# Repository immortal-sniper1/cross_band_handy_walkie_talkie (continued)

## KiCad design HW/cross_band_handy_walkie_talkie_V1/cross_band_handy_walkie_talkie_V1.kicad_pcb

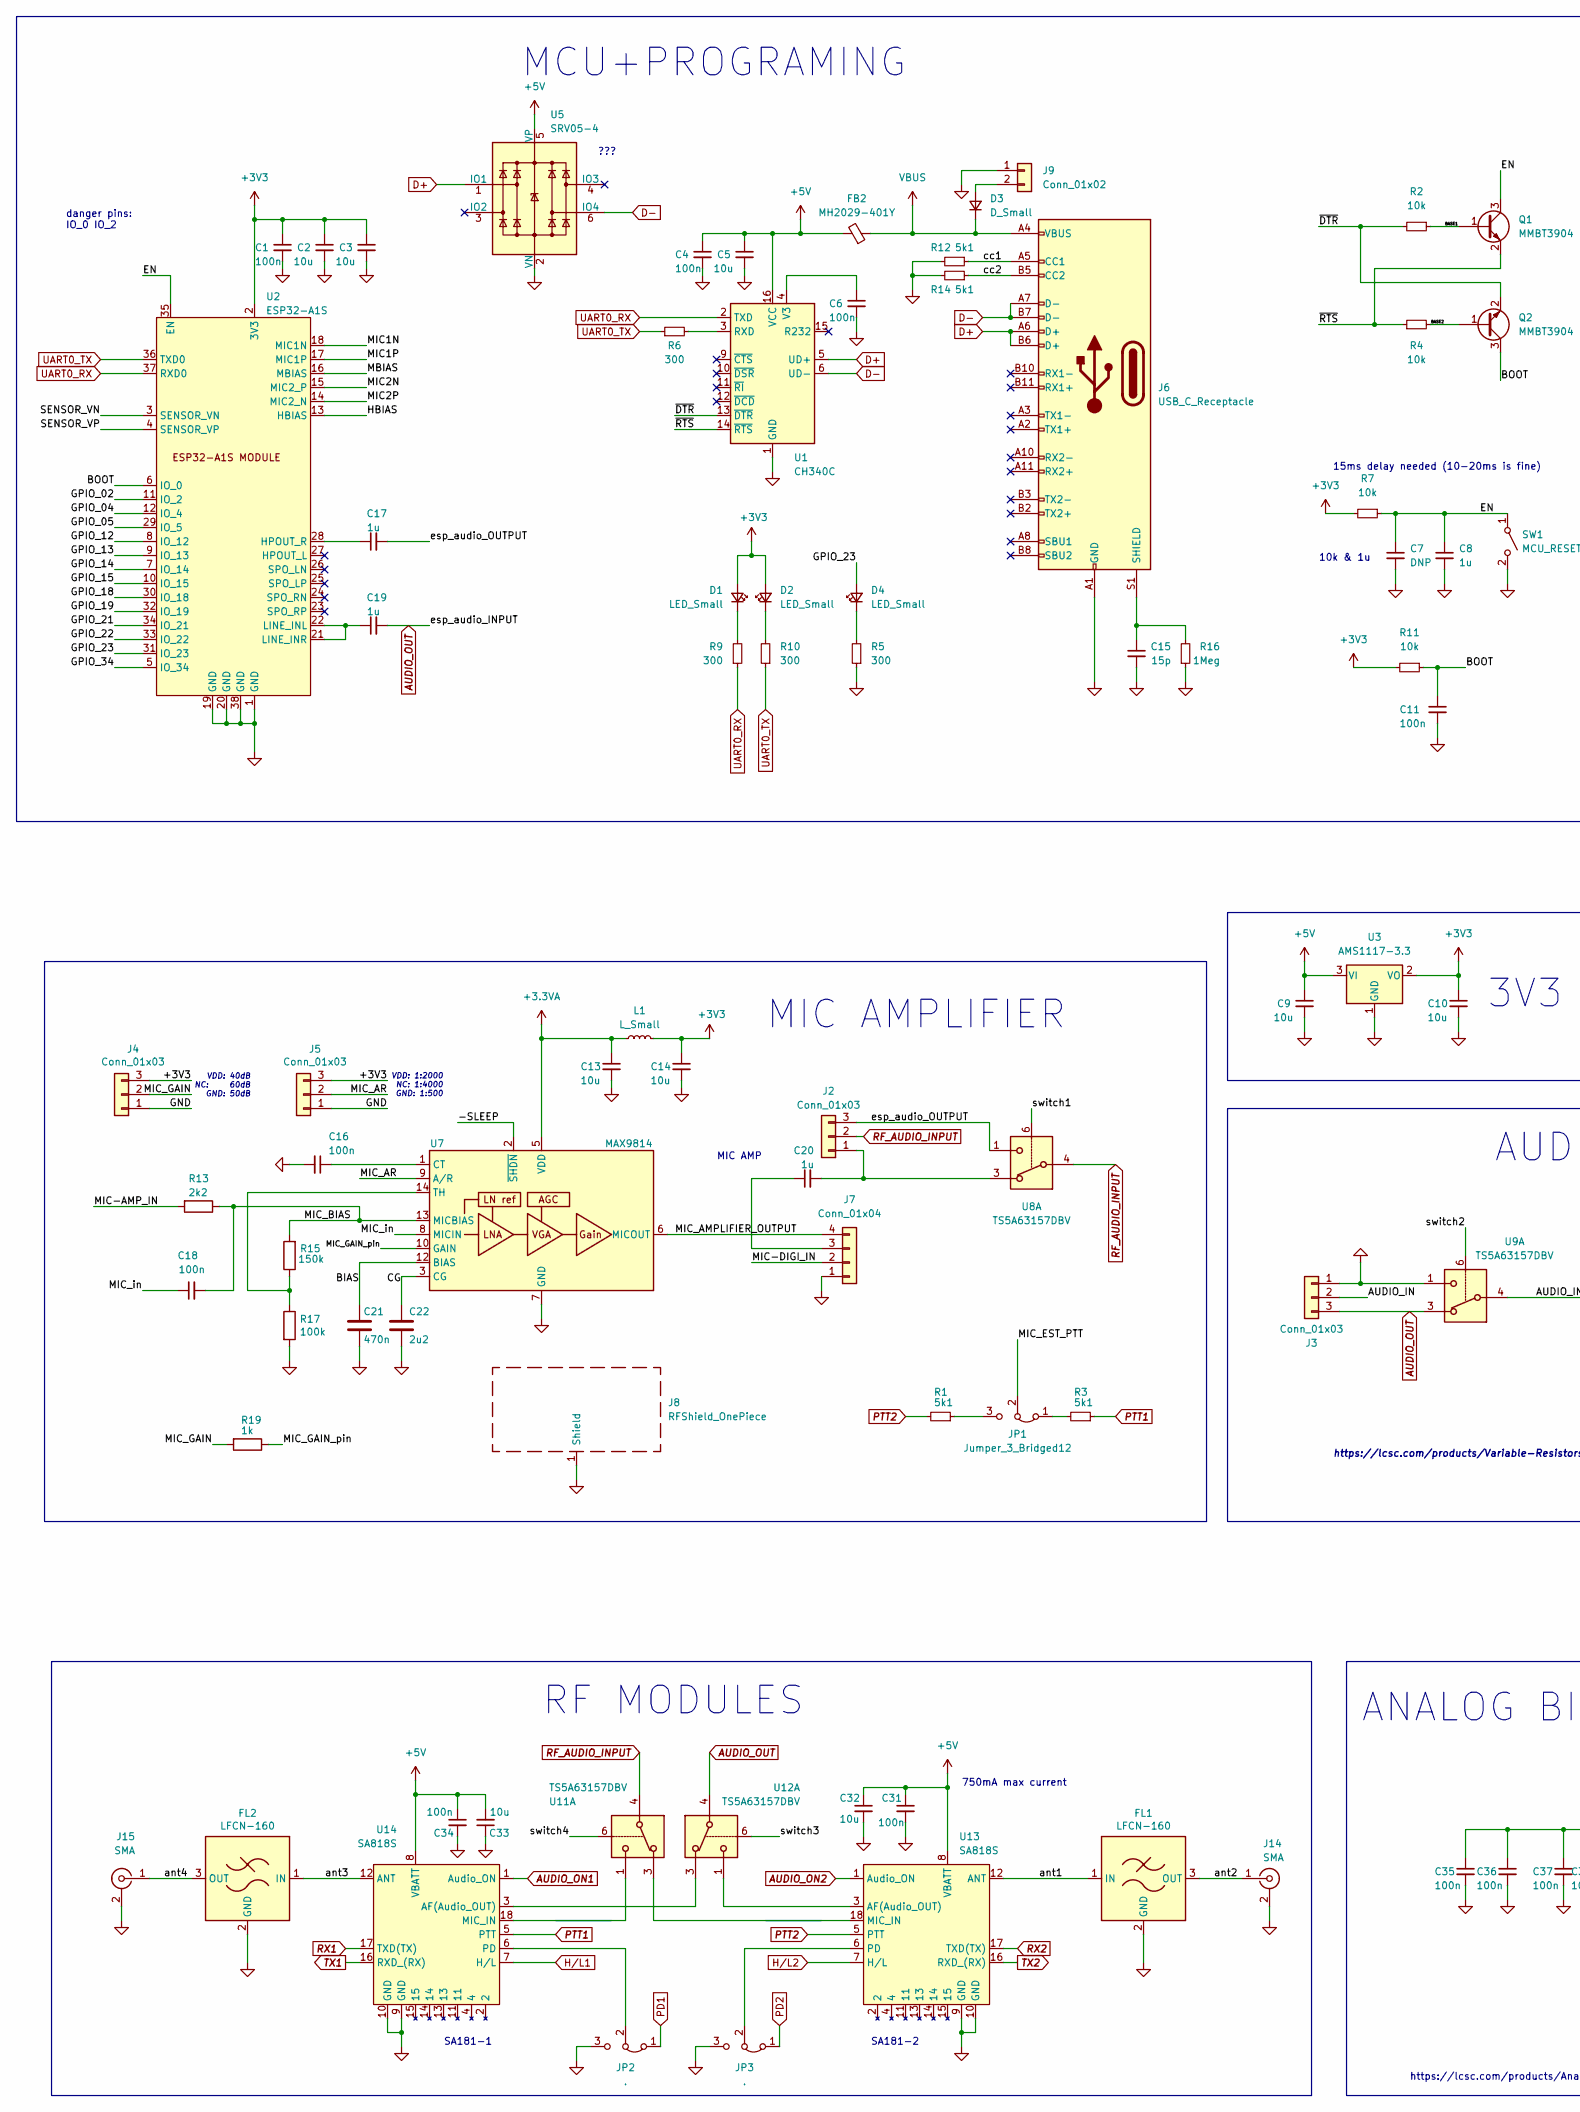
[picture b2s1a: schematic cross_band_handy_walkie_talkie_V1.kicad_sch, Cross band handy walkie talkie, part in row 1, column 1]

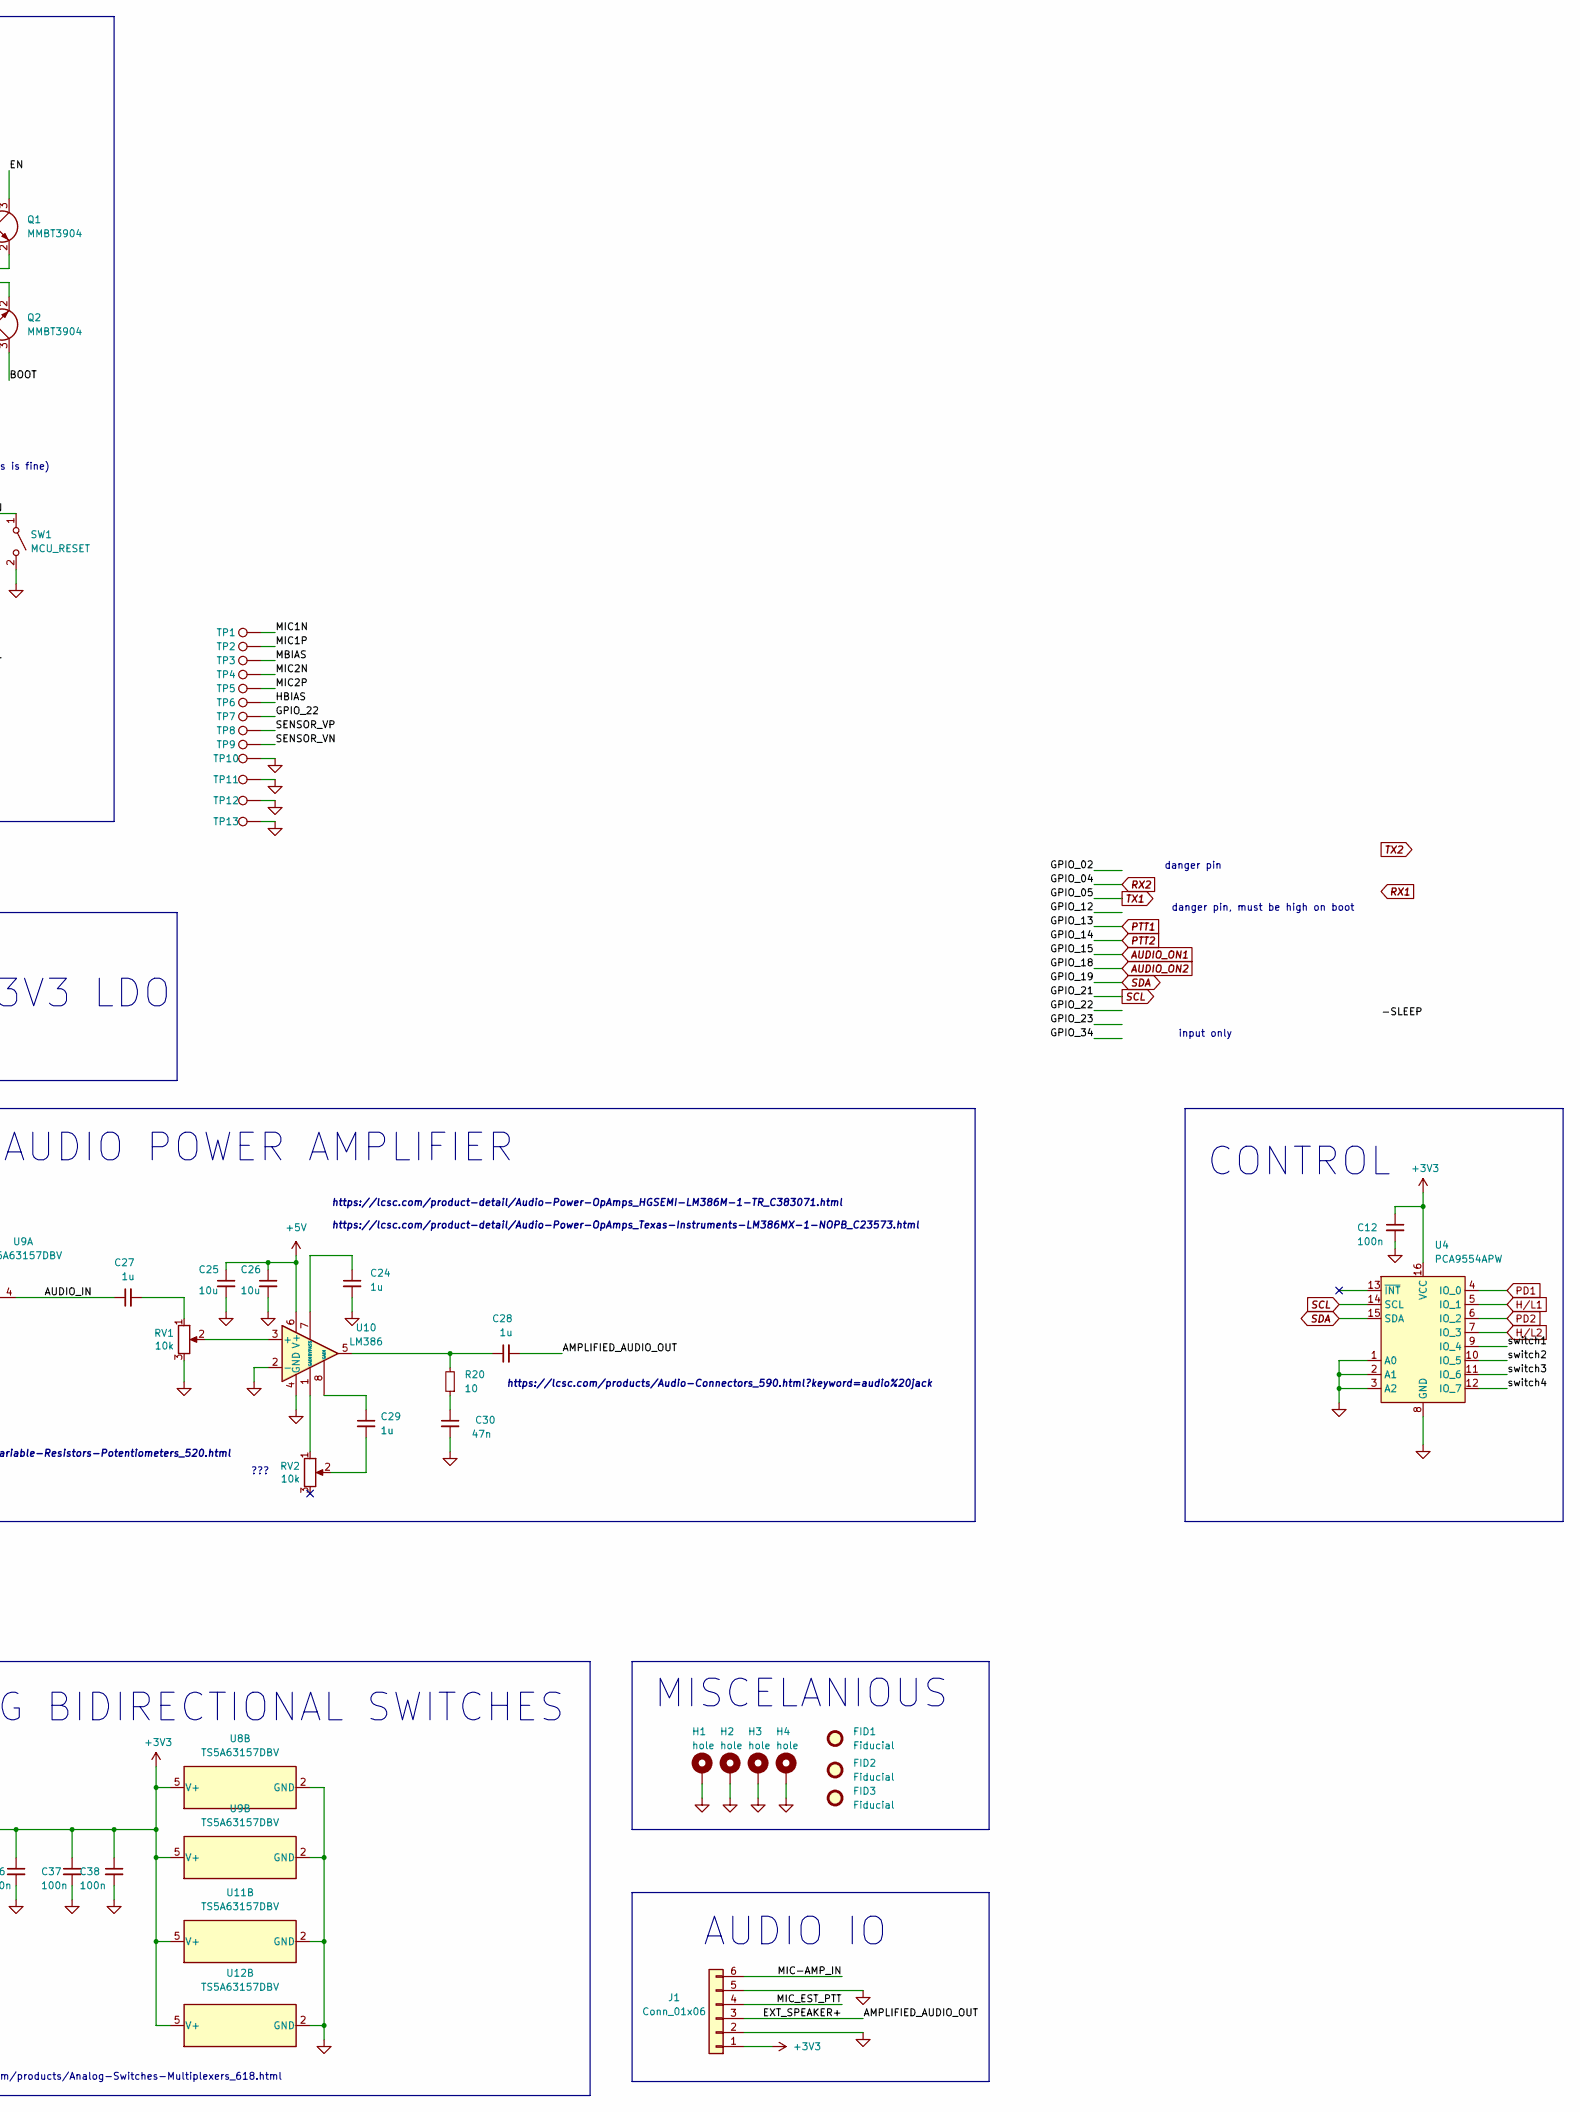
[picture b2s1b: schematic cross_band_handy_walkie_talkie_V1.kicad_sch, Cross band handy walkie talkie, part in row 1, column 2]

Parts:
C1, C4, C6, C11, C12, C16, C18, C31, C34, C35, C36, C37, C38: 100n; C_0603_1608Metric_Pad1.08x0.95mm_HandSolder; LCSC C14663
C2, C3, C5, C9, C10, C13, C14, C25, C26, C32, C33: 10u; C_0805_2012Metric; LCSC C15850
C7: DNP; C_0603_1608Metric_Pad1.08x0.95mm_HandSolder
C8, C17, C19, C20, C24, C27, C28, C29: 1u; C_0603_1608Metric_Pad1.08x0.95mm_HandSolder; LCSC C15849
C15: 15p; C_0603_1608Metric_Pad1.08x0.95mm_HandSolder; LCSC C1644
C21: 470n; C_0805_2012Metric; LCSC C13967
C22: 2u2; C_0805_2012Metric; LCSC C49217
C30: 47n; C_0603_1608Metric_Pad1.08x0.95mm_HandSolder; LCSC C1622
D1, D2, D4: LED_Small; LED_0805_2012Metric; LCSC C2297
D3: D_Small; D_SOD-123
FB2: MH2029-401Y; R_0805_2012Metric_Pad1.20x1.40mm_HandSolder
FID1: Fiducial; Fiducial_0.5mm_Mask1mm
FID2: Fiducial; KiCad-Logo2_5mm_SilkScreen
FID3: Fiducial; WEEE-Logo_4.2x6mm_SilkScreen
FL1, FL2: LFCN-160; Filter_Mini-Circuits_FV1206
H1, H2, H3, H4: hole; MountingHole_3.2mm_M3_DIN965_Pad_TopBottom
J1: Conn_01x06; PinHeader_1x06_P2.54mm_Vertical
J2, J3, J4, J5: Conn_01x03; PinHeader_1x03_P2.54mm_Vertical
J6: USB_C_Receptacle; USB_C_Receptacle_HRO_TYPE-C-31-M-12; LCSC C319148
J7: Conn_01x04; PinHeader_1x04_P2.54mm_Vertical
J8: RFShield_OnePiece; Wuerth_36103205_20x20mm
J9: Conn_01x02; PinHeader_1x02_P2.54mm_Vertical
J14, J15: SMA; SMA_Amphenol_901-144_Vertical
JP1: Jumper_3_Bridged12; PinHeader_1x03_P2.54mm_Vertical
JP2, JP3: .; SolderJumper-3_P2.0mm_Open_TrianglePad1.0x1.5mm_NumberLabels
L1: L_Small; L_0805_2012Metric; LCSC C1046
Q1, Q2: MMBT3904; SOT-23; LCSC C20526
R1, R3, R12, R14: 5k1; R_0603_1608Metric_Pad0.98x0.95mm_HandSolder; LCSC C23186
R2, R4, R7, R11: 10k; R_0603_1608Metric_Pad0.98x0.95mm_HandSolder; LCSC C25804
R5, R6, R9, R10: 300; R_0603_1608Metric_Pad0.98x0.95mm_HandSolder; LCSC C23025
R13: 2k2; R_0805_2012Metric; LCSC C17520
R15: 150k; R_0805_2012Metric; LCSC C17470
R16: 1Meg; R_0603_1608Metric_Pad0.98x0.95mm_HandSolder; LCSC C22935
R17: 100k; R_0805_2012Metric; LCSC C149504
R19: 1k; R_0805_2012Metric; LCSC C17513
R20: 10; R_0603_1608Metric_Pad0.98x0.95mm_HandSolder
RV1, RV2: 10k; Potentiometer_Bourns_3266W_Vertical; LCSC C118956
SW1: MCU_RESET; PTS526SK15SMTR2LFS; LCSC C318884
TP1, TP2, TP3, TP4, TP5, TP6, TP7, TP8, TP9, TP10, TP11, TP12, TP13: TestPoint; TestPoint_Pad_1.5x1.5mm
U1: CH340C; SOIC-16_3.9x9.9mm_P1.27mm; LCSC C84681
U2: ESP32-A1S; LCSC C277945
U3: AMS1117-3.3; SOT-223-3_TabPin2; LCSC C6186
U4: PCA9554APW; TSSOP-16_4.4x5mm_P0.65mm; LCSC C86803
U5: SRV05-4; SOT-23-6; LCSC C85364
U7: MAX9814; DFN-14-1EP_3x3mm_P0.4mm_EP1.78x2.35mm; LCSC C41714
U8, U9, U11, U12: TS5A63157DBV; SOT-23-6; LCSC C2673185
U10: LM386; SOIC-8-1EP_3.9x4.9mm_P1.27mm_EP2.41x3.3mm_ThermalVias; LCSC C383071
U13, U14: SA818S; LCSC C3001549

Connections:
+3.3VA: C13.1, L1.1, U7.5 (VDD)
+3V3: C1.1, C2.1, C3.1, C10.1, C12.1, C14.1, C35.1, C36.1, C37.1, C38.1, D1.2 (A), D2.2 (A), J1.1, J4.3, J5.3, L1.2, R7.2, R11.2, U2.2 (3V3), U3.2 (VO), U4.16 (VCC), U8.5 (V+), U9.5 (V+), U11.5 (V+), U12.5 (V+)
+5V: C4.1, C5.1, C9.1, C25.1, C26.1, C31.1, C32.1, C33.2, C34.1, FB2.2, U1.16 (VCC), U3.3 (VI), U5.5 (VP), U10.6 (V+), U13.8 (VBATT), U14.8 (VBATT)
/-SLEEP: U7.2 (~SHDN)
/AMPLIFIED_AUDIO_OUT: C28.2, J1.3
/AUDIO_IN: C27.1, J3.2, U9.4
/BASE1: Q1.1 (B), R2.1
/BASE2: Q2.1 (B), R4.2
/BIAS: C21.1, U7.12 (BIAS)
/BOOT: C11.1, Q2.3 (C), R11.1, U2.6 (IO_0)
/CG: C22.1, U7.3 (CG)
/EN: C7.1, C8.1, Q1.3 (C), R7.1, SW1.1 (A), U2.35 (EN)
/GPIO_02: U2.11 (IO_2)
/GPIO_12: U2.8 (IO_12)
/GPIO_22: TP7.1, U2.33 (IO_22)
/GPIO_23: D4.2 (A), U2.31 (IO_23)
/GPIO_34: U2.5 (IO_34)
/HBIAS: TP6.1, U2.13 (HBIAS)
/MBIAS: TP3.1, U2.16 (MBIAS)
/MIC1N: TP1.1, U2.18 (MIC1N)
/MIC1P: TP2.1, U2.17 (MIC1P)
/MIC2N: TP4.1, U2.15 (MIC2_P)
/MIC2P: TP5.1, U2.14 (MIC2_N)
/MIC-AMP_IN: J1.6, R13.2
/MIC-DIGI_IN: J7.2
/MIC_AMPLIFIER_OUTPUT: J7.4, U7.6 (MICOUT)
/MIC_AR: J5.2, U7.9 (A/R)
/MIC_BIAS: C18.2, R13.1, R15.2, U7.13 (MICBIAS)
/MIC_EST_PTT: J1.4, JP1.2 (C)
/MIC_GAIN: J4.2, R19.2
/MIC_GAIN_pin: R19.1, U7.10 (GAIN)
/MIC_in: C18.1, U7.8 (MICIN)
/SENSOR_VN: TP9.1, U2.3 (SENSOR_VN)
/SENSOR_VP: TP8.1, U2.4 (SENSOR_VP)
/ant1: FL1.1 (IN), U13.12 (ANT)
/ant2: FL1.3 (OUT), J14.1 (In)
/ant3: FL2.1 (IN), U14.12 (ANT)
/ant4: FL2.3 (OUT), J15.1 (In)
/cc1: J6.A5 (CC1), R12.1
/cc2: J6.B5 (CC2), R14.1
/esp_audio_OUTPUT: C17.2, J2.3, U8.1
/switch1: U4.9 (IO_4), U8.6
/switch2: U4.10 (IO_5), U9.6
/switch3: U4.11 (IO_6), U12.6
/switch4: U4.12 (IO_7), U11.6
/~DTR: Q2.2 (E), R2.2, U1.13 (~DTR)
/~RTS: Q1.2 (E), R4.1, U1.14 (~RTS)
AUDIO_ON1: U2.10 (IO_15), U14.1 (Audio_ON)
AUDIO_ON2: U2.30 (IO_18), U13.1 (Audio_ON)
AUDIO_OUT: C19.2, J3.3, U9.3, U12.4
D+: J6.A6 (D+), J6.B6 (D+), U1.5 (UD+), U5.1 (IO1)
D-: J6.A7 (D-), J6.B7 (D-), U1.6 (UD-), U5.6 (IO4)
GND: C1.2, C2.2, C3.2, C4.2, C5.2, C6.2, C7.2, C8.2, C9.2, C10.2, C11.2, C12.2, C13.2, C14.2, C15.2, C16.2, C21.2, C22.2, C24.2, C25.2, C26.2, C30.2, C31.2, C32.2, C33.1, C34.2, C35.2, C36.2, C37.2, C38.2, FL1.2 (GND), FL1.4 (GND), FL2.2 (GND), FL2.4 (GND), H1.1, H2.1, H3.1, H4.1, J1.2, J1.5, J3.1, J4.1, J5.1, J6.A1 (GND), J6.A12 (GND), J6.B1 (GND), J6.B12 (GND), J7.1, J8.1 (Shield), J9.1, J14.2 (Ext), J15.2 (Ext), JP2.3 (B), JP3.3 (B), R5.1, R12.2, R14.2, R16.1, R17.2, RV1.3, SW1.2 (B), TP10.1, TP11.1, TP12.1, TP13.1, U1.1 (GND), U2.1 (GND), U2.19 (GND), U2.20 (GND), U2.38 (GND), U3.1 (GND), U4.1 (A0), U4.2 (A1), U4.3 (A2), U4.8 (GND), U5.2 (VN), U7.4 (GND), U7.7 (GND), U7.11 (GND), U7.15 (GND), U8.2 (GND), U9.1, U9.2 (GND), U10.2 (-), U10.4 (GND), U11.2 (GND), U12.2 (GND), U13.9 (GND), U13.10 (GND), U14.9 (GND), U14.10 (GND)
H/L1: U4.5 (IO_1), U14.7 (H/L)
H/L2: U4.7 (IO_3), U13.7 (H/L)
unnamed: C6.1, U1.4 (V3)
unnamed: C15.1, J6.S1 (SHIELD), R16.2
unnamed: C16.1, U7.1 (CT)
unnamed: C17.1, U2.28 (HPOUT_R)
unnamed: C19.1, U2.21 (LINE_INR), U2.22 (LINE_INL)
unnamed: C20.1, J7.3
unnamed: C20.2, J2.1, U8.3
unnamed: C24.1, U10.7 (BYPASS)
unnamed: C27.2, RV1.1
unnamed: C28.1, R20.2, U10.5
unnamed: C29.1, U10.8 (GAIN)
unnamed: C29.2, RV2.2
unnamed: C30.1, R20.1
unnamed: D1.1 (K), R9.2
unnamed: D2.1 (K), R10.2
unnamed: D3.2 (A), J9.2
unnamed: D4.1 (K), R5.2
unnamed: JP1.1 (A), R3.2
unnamed: JP1.3 (B), R1.1
unnamed: R15.1, R17.1, U7.14 (TH)
unnamed: RV1.2, U10.3 (+)
unnamed: RV2.1, U10.1 (GAIN)
unnamed: R6.2, U1.3 (RXD)
unnamed: U11.1, U14.18 (MIC_IN)
unnamed: U11.3, U13.18 (MIC_IN)
unnamed: U12.1, U13.3 (AF(Audio_OUT))
unnamed: U12.3, U14.3 (AF(Audio_OUT))
unnamed: JP3.2 (C), U13.6 (PD)
unnamed: JP2.2 (C), U14.6 (PD)
PD1: JP2.1 (A), U4.4 (IO_0)
PD2: JP3.1 (A), U4.6 (IO_2)
PTT1: R3.1, U2.9 (IO_13), U14.5 (PTT)
PTT2: R1.2, U2.7 (IO_14), U13.5 (PTT)
RF_AUDIO_INPUT: J2.2, U8.4, U11.4
RX1: U14.17 (TXD(TX))
RX2: U2.12 (IO_4), U13.17 (TXD(TX))
SCL: U2.34 (IO_21), U4.14 (SCL)
SDA: U2.32 (IO_19), U4.15 (SDA)
TX1: U2.29 (IO_5), U14.16 (RXD_(RX))
TX2: U13.16 (RXD_(RX))
UART0_RX: R9.1, U1.2 (TXD), U2.37 (RXD0)
UART0_TX: R6.1, R10.1, U2.36 (TXD0)
VBUS: D3.1 (K), FB2.1, J6.A4 (VBUS), J6.A9 (VBUS), J6.B4 (VBUS), J6.B9 (VBUS)

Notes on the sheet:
3V3 LDO
MISCELANIOUS
https://lcsc.com/products/Audio-Connectors_590.html?keyword=audio%20jack
https://lcsc.com/product-detail/Audio-Power-OpAmps_HGSEMI-LM386M-1-TR_C383071.html https://lcsc.com/product-detail/Audio-Power-OpAmps_Texas-Instruments-LM386MX-1-NOPB_C23573.html
???
danger pins: IO_0 IO_2
https://lcsc.com/products/Variable-Resistors-Potentiometers_520.html
SA181-2
VDD: 1:2000 NC: 1:4000 GND: 1:500
danger pin
SA181-1
input only
15ms delay needed (10-20ms is fine)
MIC AMP
ANALOG BIDIRECTIONAL SWITCHES
RF MODULES
MCU+PROGRAMING
AUDIO POWER AMPLIFIER
MIC AMPLIFIER
10k & 1u
750mA max current
CONTROL
AUDIO IO
???
VDD: 40dB NC: 60dB GND: 50dB
danger pin, must be high on boot
https://lcsc.com/products/Analog-Switches-Multiplexers_618.html

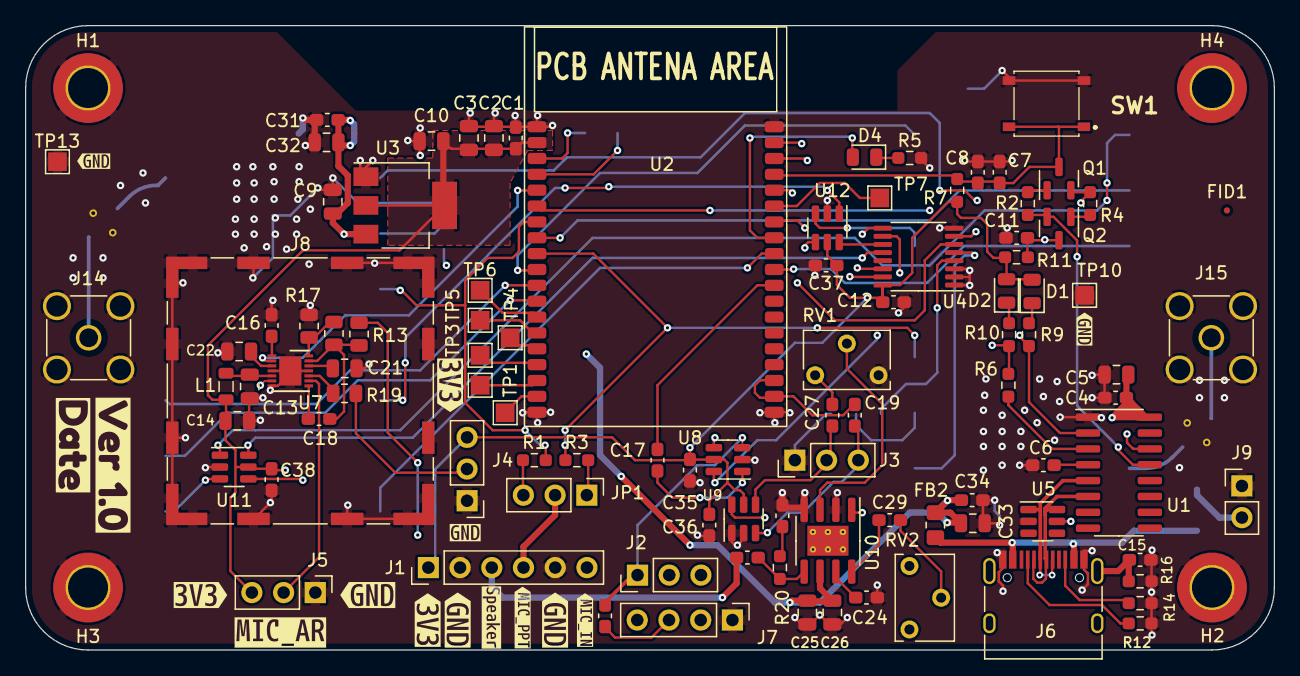
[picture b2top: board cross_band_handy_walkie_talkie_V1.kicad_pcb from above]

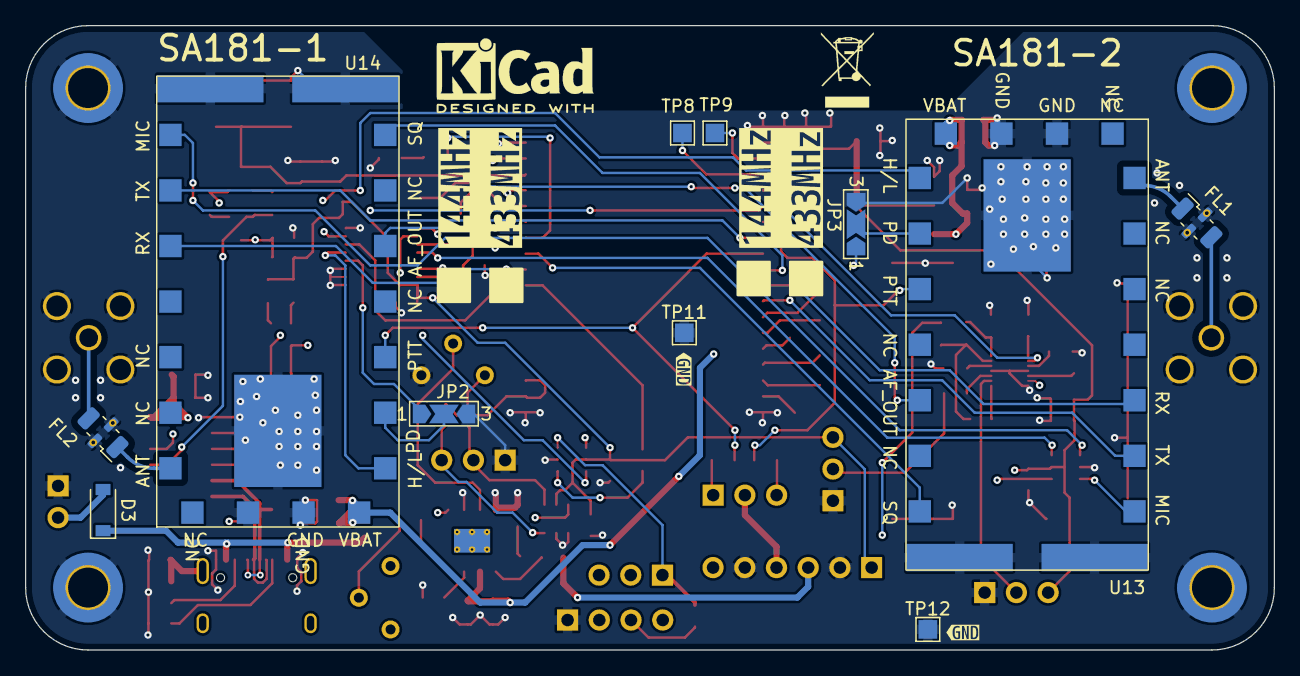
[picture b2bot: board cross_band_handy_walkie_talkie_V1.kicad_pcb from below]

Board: 4 copper layers, 100.0 x 50.0 mm, 134 parts (17 on the bottom side), 91 nets.

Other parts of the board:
kibuzzard-63C04C05: G***; kibuzzard-63C04C05
kibuzzard-63C0517C, kibuzzard-63C0517C#2, kibuzzard-63C0517C#3, kibuzzard-63C0517C#4: G***; kibuzzard-63C0517C
kibuzzard-639A1F7F, kibuzzard-639A1F7F#2, kibuzzard-639A1F7F#3: G***; kibuzzard-639A1F7F
kibuzzard-639A1F94: G***; kibuzzard-639A1F94
kibuzzard-639A1FDB: G***; kibuzzard-639A1FDB
kibuzzard-639A1FE7: G***; kibuzzard-639A1FE7
kibuzzard-639A20B2, kibuzzard-639A20B2#2: G***; kibuzzard-639A20B2
kibuzzard-639A20C5: G***; kibuzzard-639A20C5
kibuzzard-639A25E0, kibuzzard-639A25E0#2: G***; kibuzzard-639A25E0
kibuzzard-639A26B5: G***; kibuzzard-639A26B5
kibuzzard-639A2114: G***; kibuzzard-639A2114
kibuzzard-639A2692: G***; kibuzzard-639A2692

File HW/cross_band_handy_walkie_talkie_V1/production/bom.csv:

Designator,Footprint,Quantity,Value,LCSC Part #
J5,PinHeader_1x03_P2.54mm_Vertical,1,Conn_01x03,
C7,C_0603_1608Metric_Pad1.08x0.95mm_HandSolder,1,DNP,
J3,PinHeader_1x03_P2.54mm_Vertical,1,Conn_01x03,
C10,C_0805_2012Metric,1,10u,C15850
RV1,Potentiometer_Bourns_3266W_Vertical,1,10k,C118956
R2,R_0603_1608Metric_Pad0.98x0.95mm_HandSolder,1,10k,C25804
C29,C_0603_1608Metric_Pad1.08x0.95mm_HandSolder,1,1u,C15849
R4,R_0603_1608Metric_Pad0.98x0.95mm_HandSolder,1,10k,C25804
J2,PinHeader_1x03_P2.54mm_Vertical,1,Conn_01x03,
C28,C_0603_1608Metric_Pad1.08x0.95mm_HandSolder,1,1u,C15849
R10,R_0603_1608Metric_Pad0.98x0.95mm_HandSolder,1,300,C23025
C4,C_0603_1608Metric_Pad1.08x0.95mm_HandSolder,1,100n,C14663
U11,SOT-23-6,1,TS5A63157DBV,C2673185
C38,C_0603_1608Metric_Pad1.08x0.95mm_HandSolder,1,100n,C14663
C6,C_0603_1608Metric_Pad1.08x0.95mm_HandSolder,1,100n,C14663
C18,C_0603_1608Metric_Pad1.08x0.95mm_HandSolder,1,100n,C14663
J7,PinHeader_1x04_P2.54mm_Vertical,1,Conn_01x04,
D4,LED_0805_2012Metric,1,LED_Small,C2297
R1,R_0603_1608Metric_Pad0.98x0.95mm_HandSolder,1,5k1,C23186
U4,TSSOP-16_4.4x5mm_P0.65mm,1,PCA9554APW,C86803
C3,C_0805_2012Metric,1,10u,C15850
C5,C_0805_2012Metric,1,10u,C15850
C20,C_0603_1608Metric_Pad1.08x0.95mm_HandSolder,1,1u,C15849
C27,C_0603_1608Metric_Pad1.08x0.95mm_HandSolder,1,1u,C15849
SW1,PTS526SK15SMTR2LFS,1,MCU_RESET,C318884
R20,R_0603_1608Metric_Pad0.98x0.95mm_HandSolder,1,10,
R3,R_0603_1608Metric_Pad0.98x0.95mm_HandSolder,1,5k1,C23186
U8,SOT-23-6,1,TS5A63157DBV,C2673185
D1,LED_0805_2012Metric,1,LED_Small,C2297
C19,C_0603_1608Metric_Pad1.08x0.95mm_HandSolder,1,1u,C15849
C11,C_0603_1608Metric_Pad1.08x0.95mm_HandSolder,1,100n,C14663
C12,C_0603_1608Metric_Pad1.08x0.95mm_HandSolder,1,100n,C14663
U9,SOT-23-6,1,TS5A63157DBV,C2673185
U2,ESP32-A1S,1,ESP32-A1S,C277945
U12,SOT-23-6,1,TS5A63157DBV,C2673185
U3,SOT-223-3_TabPin2,1,AMS1117-3.3,C347222
C33,C_0805_2012Metric,1,10u,C15850
C17,C_0603_1608Metric_Pad1.08x0.95mm_HandSolder,1,1u,C15849
R17,R_0805_2012Metric,1,100k,C149504
C16,C_0603_1608Metric_Pad1.08x0.95mm_HandSolder,1,100n,C14663
C24,C_0603_1608Metric_Pad1.08x0.95mm_HandSolder,1,1u,C15849
C32,C_0805_2012Metric,1,10u,C15850
C34,C_0603_1608Metric_Pad1.08x0.95mm_HandSolder,1,100n,C14663
J15,SMA_Amphenol_901-144_Vertical,1,SMA,
C21,C_0805_2012Metric,1,470n,C13967
J4,PinHeader_1x03_P2.54mm_Vertical,1,Conn_01x03,
Q1,SOT-23,1,MMBT3904,C20526
RV2,Potentiometer_Bourns_3266W_Vertical,1,10k,C118956
C30,C_0603_1608Metric_Pad1.08x0.95mm_HandSolder,1,47n,C1622
C2,C_0805_2012Metric,1,10u,C15850
U10,SOIC-8-1EP_3.9x4.9mm_P1.27mm_EP2.41x3.3mm_ThermalVias,1,LM386,C383071
R15,R_0805_2012Metric,1,150k,C17470
C26,C_0805_2012Metric,1,10u,C15850
C31,C_0603_1608Metric_Pad1.08x0.95mm_HandSolder,1,100n,C14663
J14,SMA_Amphenol_901-144_Vertical,1,SMA,
C13,C_0805_2012Metric,1,10u,C15850
C15,C_0603_1608Metric_Pad1.08x0.95mm_HandSolder,1,15p,C1644
C14,C_0805_2012Metric,1,10u,C15850
C9,C_0805_2012Metric,1,10u,C15850
R11,R_0603_1608Metric_Pad0.98x0.95mm_HandSolder,1,10k,C25804
C22,C_0805_2012Metric,1,2u2,C49217
L1,L_0805_2012Metric,1,L_Small,C1046
J1,PinHeader_1x06_P2.54mm_Vertical,1,Conn_01x06,
U1,SOIC-16_3.9x9.9mm_P1.27mm,1,CH340C,C84681
JP1,PinHeader_1x03_P2.54mm_Vertical,1,Jumper_3_Bridged12,
R9,R_0603_1608Metric_Pad0.98x0.95mm_HandSolder,1,300,C23025
R19,R_0805_2012Metric,1,1k,C17513
FB2,R_0805_2012Metric_Pad1.20x1.40mm_HandSolder,1,MH2029-401Y,
R14,R_0603_1608Metric_Pad0.98x0.95mm_HandSolder,1,5k1,C23186
R12,R_0603_1608Metric_Pad0.98x0.95mm_HandSolder,1,5k1,C23186
C1,C_0603_1608Metric_Pad1.08x0.95mm_HandSolder,1,100n,C14663
J9,PinHeader_1x02_P2.54mm_Vertical,1,Conn_01x02,
Q2,SOT-23,1,MMBT3904,C20526
C37,C_0603_1608Metric_Pad1.08x0.95mm_HandSolder,1,100n,C14663
R16,R_0603_1608Metric_Pad0.98x0.95mm_HandSolder,1,1Meg,C22935
C35,C_0603_1608Metric_Pad1.08x0.95mm_HandSolder,1,100n,C14663
D2,LED_0805_2012Metric,1,LED_Small,C2297
C8,C_0603_1608Metric_Pad1.08x0.95mm_HandSolder,1,15n,C1644
R13,R_0805_2012Metric,1,2k2,C17520
R7,R_0603_1608Metric_Pad0.98x0.95mm_HandSolder,1,1Meg,C22935
J6,USB_C_Receptacle_HRO_TYPE-C-31-M-12,1,USB_C_Receptacle,C319148
R5,R_0603_1608Metric_Pad0.98x0.95mm_HandSolder,1,300,C23025
C25,C_0805_2012Metric,1,10u,C15850
C36,C_0603_1608Metric_Pad1.08x0.95mm_HandSolder,1,100n,C14663
U7,DFN-14-1EP_3x3mm_P0.4mm_EP1.78x2.35mm,1,MAX9814,C41714
FL2,Filter_Mini-Circuits_FV1206,1,LFCN-160,
D3,D_SOD-123,1,D_Small,
U14,SA818S,1,SA818S,C3001549
FL1,Filter_Mini-Circuits_FV1206,1,LFCN-160,
U13,SA818S,1,SA818S,C3001549

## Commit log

2022-12-19 gerber
2023-01-08 test1
2023-05-31 Walkie Talkie DRAFT
2023-06-14 Update fp-info-cache
